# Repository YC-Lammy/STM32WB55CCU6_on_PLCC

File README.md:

# STM32WB55CCU6_on_PLCC

STM32WB55CCU6 on a PLCC board for development use. a chip antenna and MPU-6050 on board.

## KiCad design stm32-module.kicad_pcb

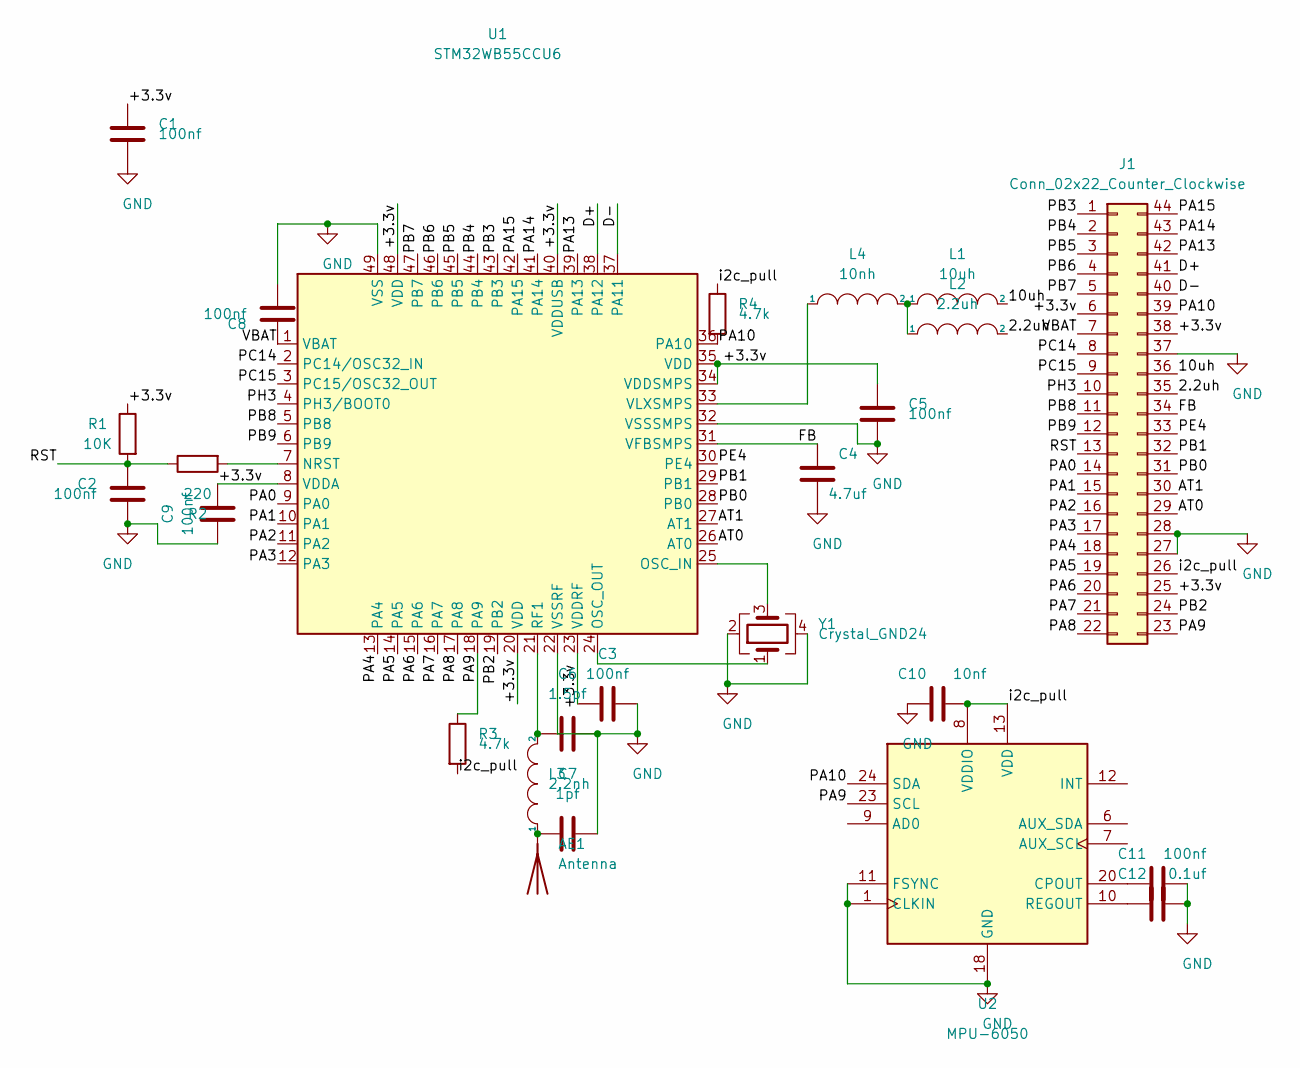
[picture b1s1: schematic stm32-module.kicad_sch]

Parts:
AE1: Antenna; R_1206_3216Metric
C1, C2, C3, C5, C8, C9, C11: 100nf; C_0402_1005Metric
C4: 4.7uf; C_0402_1005Metric
C6: 1.5pf; C_0402_1005Metric
C7: 1pf; C_0402_1005Metric
C10: 10nf; C_0402_1005Metric
C12: 0.1uf; C_0402_1005Metric
J1: Conn_02x22_Counter_Clockwise; PLCC-44_16.6x16.6mm_P1.27mm
L1: 10uh; L_0603_1608Metric
L2: 2.2uh; L_0805_2012Metric
L3: 2.2nh; L_0603_1608Metric
L4: 10nh; L_0603_1608Metric
R1: 10K; C_0201_0603Metric
R2: 220; R_0201_0603Metric
R3, R4: 4.7k; R_0402_1005Metric
U1: STM32WB55CCU6; QFN-48-1EP_7x7mm_P0.5mm_EP5.6x5.6mm
U2: MPU-6050; InvenSense_QFN-24_4x4mm_P0.5mm
Y1: Crystal_GND24; Crystal_SMD_3225-4Pin_3.2x2.5mm

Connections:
/2.2uh: J1.35, L2.2
/10uh: J1.36, L1.2
/+3.3v: C1.1, C3.1, C5.1, C9.2, J1.6, J1.25, J1.38, R1.1, U1.8 (VDDA), U1.20 (VDD), U1.23 (VDDRF), U1.34 (VDDSMPS), U1.35 (VDD), U1.40 (VDDUSB), U1.48 (VDD)
/AT0: J1.29, U1.26 (AT0)
/AT1: J1.30, U1.27 (AT1)
/D+: J1.41, U1.38 (PA12)
/D-: J1.40, U1.37 (PA11)
/FB: C4.1, J1.34, U1.31 (VFBSMPS)
/PA0: J1.14, U1.9 (PA0)
/PA1: J1.15, U1.10 (PA1)
/PA2: J1.16, U1.11 (PA2)
/PA3: J1.17, U1.12 (PA3)
/PA4: J1.18, U1.13 (PA4)
/PA5: J1.19, U1.14 (PA5)
/PA6: J1.20, U1.15 (PA6)
/PA7: J1.21, U1.16 (PA7)
/PA8: J1.22, U1.17 (PA8)
/PA9: J1.23, R3.1, U1.18 (PA9), U2.23 (SCL)
/PA10: J1.39, R4.2, U1.36 (PA10), U2.24 (SDA)
/PA13: J1.42, U1.39 (PA13)
/PA14: J1.43, U1.41 (PA14)
/PA15: J1.44, U1.42 (PA15)
/PB0: J1.31, U1.28 (PB0)
/PB1: J1.32, U1.29 (PB1)
/PB2: J1.24, U1.19 (PB2)
/PB3: J1.1, U1.43 (PB3)
/PB4: J1.2, U1.44 (PB4)
/PB5: J1.3, U1.45 (PB5)
/PB6: J1.4, U1.46 (PB6)
/PB7: J1.5, U1.47 (PB7)
/PB8: J1.11, U1.5 (PB8)
/PB9: J1.12, U1.6 (PB9)
/PC14: J1.8, U1.2 (PC14/OSC32_IN)
/PC15: J1.9, U1.3 (PC15/OSC32_OUT)
/PE4: J1.33, U1.30 (PE4)
/PH3: J1.10, U1.4 (PH3/BOOT0)
/RST: C2.1, J1.13, R1.2, R2.1
/VBAT: C8.1, J1.7, U1.1 (VBAT)
/i2c_pull: C10.2, J1.26, R3.2, R4.1, U2.8 (VDDIO), U2.13 (VDD); also elsewhere on the board
GND: C1.2, C2.2, C3.2, C4.2, C5.2, C6.1, C7.2, C8.2, C9.1, C10.1, C11.2, C12.2, J1.27, J1.28, J1.37, U1.22 (VSSRF), U1.32 (VSSSMPS), U1.49 (VSS), U2.1 (CLKIN), U2.11 (FSYNC), U2.18 (GND), Y1.2, Y1.4; also elsewhere on the board
unnamed: AE1.1 (A), C7.1, L3.1
unnamed: C6.2, L3.2, U1.21 (RF1)
unnamed: C11.1, U2.20 (CPOUT)
unnamed 43: C12.1, U2.10 (REGOUT); also elsewhere on the board
unnamed: L1.1, L2.1, L4.2
unnamed: L4.1, U1.33 (VLXSMPS)
unnamed: R2.2, U1.7 (NRST)
unnamed: U1.24 (OSC_OUT), Y1.1
unnamed: U1.25 (OSC_IN), Y1.3

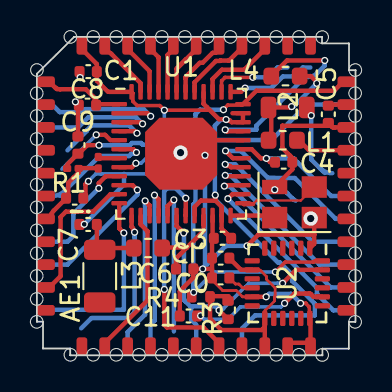
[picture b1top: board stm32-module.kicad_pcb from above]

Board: 2 copper layers, 17.7 x 17.7 mm, 25 parts (0 on the bottom side), 49 nets.

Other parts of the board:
C0: 0.1uf; C_0402_1005Metric
CΙ': 10nf; C_0402_1005Metric

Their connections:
/i2c_pull: CΙ'.2; also elsewhere on the board
GND: C0.2, CΙ'.1; also elsewhere on the board
unnamed 43: C0.1; also elsewhere on the board
